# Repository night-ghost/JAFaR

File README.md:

The original pkendall64 version not works or even not compiles for me so this is easy-build version with almost the same functions

## pkendall64's original README follows

# JAFaR (Just Another Fatshark Receiver Module)

DIY OpenSource 40ch receiver OSD integrated

## This is a major refactor of MikyM0use's original code

**Changes**
* Added a favorites section which remembers the last 8 channels used ordered with the last used at the top of the list. It re-orders the list when you select a new channel.
* The scanner is continuously running in the main menu or scanner menu. This means that the RSSI values are pretty much always up to date.
* There's a timer progress bar on the right rather than a counter.
* Double-click (i.e. another press within 1 second) takes you back to the main menu.
* When in a band selection menu, favorites or autoscan a single click of the buttons selects the next or previous channel respectively.
* When a channel is selected, display the current RSSI for each receiver under the channel designator (only on the OLED display).
* Moved all strings in OLED and OSD to PROGMEM.

Make sure to use the updated TVout library from https://github.com/pkendall64/arduino-tvout as the original will cancel timer 2, which is the selection timer for this version of the receiver.

## MikyM0use's original README follows

The aim of the project is to build an opensource 40ch receiver for Fatshark goggles which has to be easy to develop,
upgrade and maintain. And, of course, it must be cheap!

* 40ch (8 channels for 5 bands, including race band)
* No external switch, or hall effect sensor, or buzzer, it must use __only__ the goggles buttons (up-down)
* Auto search feature
* It should include the “scanner” feature (see my recent project here https://github.com/MikyM0use/OLED-scanner)
* Frequency selection via OSD inside the goggles
* I tested it only with Fatshark HD but the module should work with every Fatshark with the RX external module (like Dominator V1, V2, V3, HD, HD2...)

This project uses the “RX5808” receiver module, which can be hacked to be SPI-programmed by a microcontroller (more details later).
So what I needed is a micro controller with an easy and well-know software IDE… nothing better than Arduino. So I decided to use an Atmega 328p as micro controller.

To select the frequency there's a series of menus on the screen inside the goggles, the
useful TVOUT Arduino library is perfect and requires just a couple of resistors
(http://playground.arduino.cc/Main/TVout).
A digital switch (TS5A3359) allow to switch from OSD to the normal receiving video from the quadcopter.

The project is mainly divided into two PCBs:
* one main base module
* one "diversity" daughterboard (optional)

it's also possibile to use an SPI-OLED display and use the module as standalone RX.

##Table of contents
* [Main module](#main-module)
	* [DIY Instructions](#diy-instructions)
	* [MAIN MODULE Troubleshooting](#main-module-troubleshooting)
* [Diversity module](#diversity-module)
* [OLED module](#oled-module)
* [STANDALONE mode](#standalone-mode)
* [Reference thread](#reference-thread)
* [FAQ:](#faq)
* [Donations:](#donations)

##Main module

This is the main RX module, usable alone as a 40ch receiver module, but if you connect an
"external" module, the onboard microcontroller can decide which RX module has better
reception (so-called "diversity") based on the received signal strength. Indeed, this
RX5808 modules has an analog output called RSSI proportional on the "quality" of the
received video signal. The receiving video channel (frequency) is set by the user using an OSD menu.

__MAIN MODULE (V4.0) BOM__

https://docs.google.com/spreadsheets/d/1CrZzOQHyK_d1VfHCQKwdNuoyMji0IYryI1VuffojdGA/edit?usp=sharing

__LEGACY MAIN MODULE (V3.2)__

This module is actually the same as the v4.0, but it doesn't have the buffer on the RSSI output,
and the PCB allows the use of a capacitor OR a resistor on the video out. DON'T use both! after some
tests I realized that a 10ohm resistor (and no cap) is enough.

(the back side is the same of the v4.0).

__LEGACY MAIN MODULE (V3.2) BOM__

https://docs.google.com/spreadsheets/d/1-763imBV3QsQ71GKDZH-BirTz1k32szNuJZUKQrE00g/edit?usp=sharing

###DIY Instructions

1. Remove the shield of the RX5808 module and desolder the resistor marked by the arrow. This
is the SPI-mod required to control the module with an external microcontroller.

2. Follow the instructions on the page https://www.arduino.cc/en/Tutorial/ArduinoISP to burn the bootloader (select __"Arduino Pro Mini 5v 16MHz"__ as target board)
using the pins in the upper right corner of the board

3. Use the FTDI connections in the left side of the board to upload the code present in the
Github page of the project. Please remember to copy all the subfolders of "libs" dir in the
libraries folder of Arduino (e.g. /Arduino/libraries).
Here you can find more infos and alternative methods to import the libraries:
https://www.arduino.cc/en/Guide/Libraries

4. When you power on the module, BOTH the leds (upper left corner of the pcb) must be on, and you must see a relatively stable splash screen for about 5 seconds

5. The very first time you power on the module, it need to calibrate itself. So please turn on the module with a working Vtx a couple of meter away (the video frequency doesn't matter). This process can take a while (about 30-50 seconds).

6. You can now use the "selection" buttons on the goggles to scroll up/down the menu to select the band

7. After the timout of the countdown (upper left corner of the screen) you entered the frequency selection (of the selected band)

8. Scroll up/down to select the frequency and wait the timeout

9. At this moment only one led on the module has to be ON, it means that the RX video output is routed to the video_input of the goggles. If you have a Vtx near, you should see the video coming from it.

10. If you press the "selection" buttons of the goggles now, you change the frequency by the 8 frequencies of the previously selected band.

###MAIN MODULE Troubleshooting

After the initial calibration, the module must turn on in couple of seconds and you must see the splash screen for some seconds before the "band selection" screen.
In the "band selection" screen you can see the 5 bands with the percentage of the maximum RSSI detected on that band. At least one of the band must be at 98-100%.
If you "enter" one band, every channel must shows a different percentage of RSSI, otherwise the SPI-mod of the module could be failed.

__Unable to flash/Aduino issues:__

(thanks to pHysiX for the help in this section!)
Got the error "no reply" when trying to load the firmware:
the ATmega microcontroller is not soldered properly / there is a short on some pins.
try a quick solder, clean and reflow.

Got the error "incorrect signature" when trying to load the firmware:
This means Arduino is able to pick up the ATMega, but it was not communicating as expected.
This is related to poor soldering of the crystal. It's possible to do the crystal using
an iron, but I strongly recommend using flow method/hot air to do this, to make sure you
don't short the three legs accidentally onto the metal case.

__Display issues:__

They are mostly related to poor soldering for the OSD components on the board. Go back and
reflow especially the Switch, and then just make sure to clean up and touch up all the caps
and resistors near and around the switch.

If you have an external monitor, you can bypass the digital switch by power on the module with external 5v and connecting the "video in" of the monitor on the test point marked in yellow the picture:

and you should see the splash screen and the menu.

If you connect the "video in" of the monitor to the test point marked in green, you should see the initial scanning (used to determine the % of the RSSI on each channel), this means a sequence of different "fogs" and (at least) one "good" image (for a fraction of second), if you have a Vtx + cam transmitting.

__Frequency issues:__

If the module is having trouble Setting Frequency, or you are not getting video when you are
on the right channel and frequency, make sure the SPI mod has been done, and that the RX5808
is soldered on well. Pretty hard to mess this part up.

##Diversity module

The diversity module is an optional second receiver, connected to the "main" base module, it has:
* integrated linear 5v regulator with ENABLE feature connected to the VCC of the main module.
In fact power a second module from the internal goggles voltage regulator IS VERY DANGEROUS!
* an optional operational buffer for RSSI signal (I noticed that lately modules seems to be more delicate)

please notice that because of the linear regulator it's not possibile to use a 3s battery to power the diversity module.

__DIVERSITY MODULE (V2.1) BOM__

https://docs.google.com/spreadsheets/d/1OpagubuxicmGTKqOHWwWdxZxY6wCs_DZqTYRxVoD4Tc/edit?usp=sharing

##OLED module
It's possible to use an external SPI OLED module in case of any problems with the internal OSD
or to use the module with an external monitor / different goggles.

It's important that the module has only SDA/SCL/RES/DC pins.

To use the OLED module instead of the internal OSD, uncomment  the line:

```
#define USE_OLED
```

in the file const.h

please remember to comment #define USE_DIVERSITY!

__Connections__

| ATMEGA328p pin        |  PCB silkscreen name           | OLED silkscreen name  |
| :-------------------:	|:------------------------------:| :--------------------:|
| VCC      				| 		EN 						| 		VCC 			|
| GND      				| GND 							| 					GND |
| 8      				| SSEL 							| 				SCL 	|
| A1      				| RSSI      					|   		SDA 		|
| A4 					|  NOT CONNECTED      			|    	NOT CONNECTED 	|
| 11 					| SDA      						|    DC 				|
| 13				 	| CLK      						|    RESET 				|

...or graphically:

there's also a "PCB" inside the PCBs folder, but it's just a simple adaptor.

##Standalone mode

It's possible to use the project also as a standalone receiver to be used in combination
with any external monitor or other kind of goggles.

In this case you must uncomment the line

```
#define STANDALONE
```

in the file const.h. You can use the standalone mode either with OSD or with the external SPI OLED module.

to change band/channel, the connections are the following (every normally-open momentary switch will do the job):

##Reference thread

http://www.rcgroups.com/forums/showthread.php?t=2619124 while I'm still writing the readme :)

##FAQ

why the OSD is on the blank screen?
it’s simpler because one cannot have to recognize the vsync and the hsync pulses.

why the switch is so small and hard to solder?!?
I need a small 3-way switch, if you have a "simpler" one, just tell me :)

please note that you try and use this project AT YOUR OWN RISK!

##Donations

Hardware or paypal donations to carry on the project are always accepted.

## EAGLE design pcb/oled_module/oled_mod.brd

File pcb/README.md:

PLEASE READ THIS BEFORE GO FURTHER!

THIS PCB IS VERY EXPERIMENTAL! TRY IT AT YOUR OWN RISK!

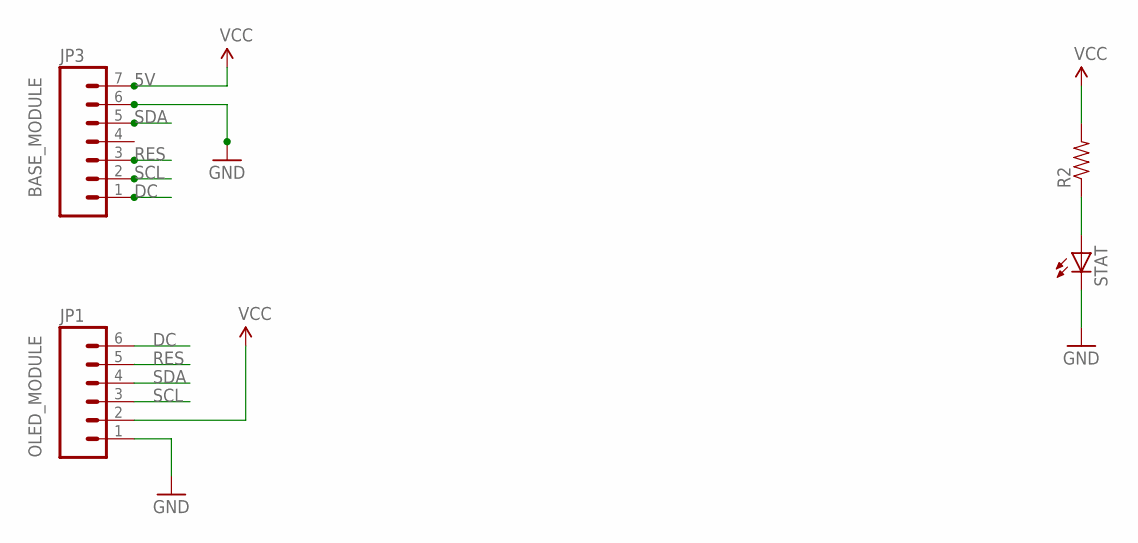
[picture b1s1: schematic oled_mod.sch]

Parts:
JP1: M06SILK_FEMALE_PTH; 1X06
JP3: M07; 1X07
R2: RESISTOR0805-RES; 0805
STAT: LEDCHIP-LED0805; CHIP-LED0805

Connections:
5V: JP1.2, JP3.7, R2.2
DC: JP1.6, JP3.1
GND: JP1.1, JP3.6, STAT.C
unnamed: R2.1, STAT.A
RES: JP1.5, JP3.3
SCL: JP1.3, JP3.2
SDA: JP1.4, JP3.5

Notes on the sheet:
BASE_MODULE
OLED_MODULE

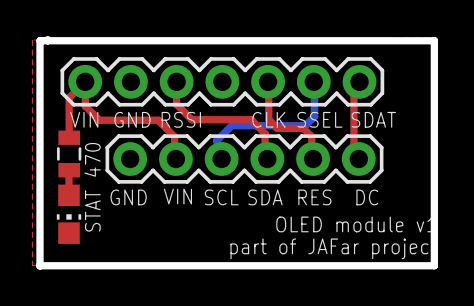
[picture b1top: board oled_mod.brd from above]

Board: 2 copper layers, 21.9 x 12.6 mm, 4 parts (0 on the bottom side), 7 nets.

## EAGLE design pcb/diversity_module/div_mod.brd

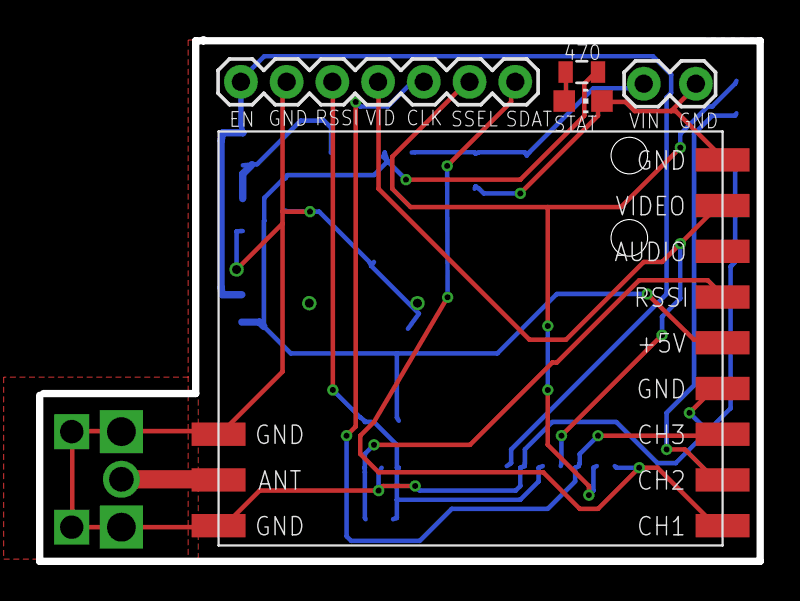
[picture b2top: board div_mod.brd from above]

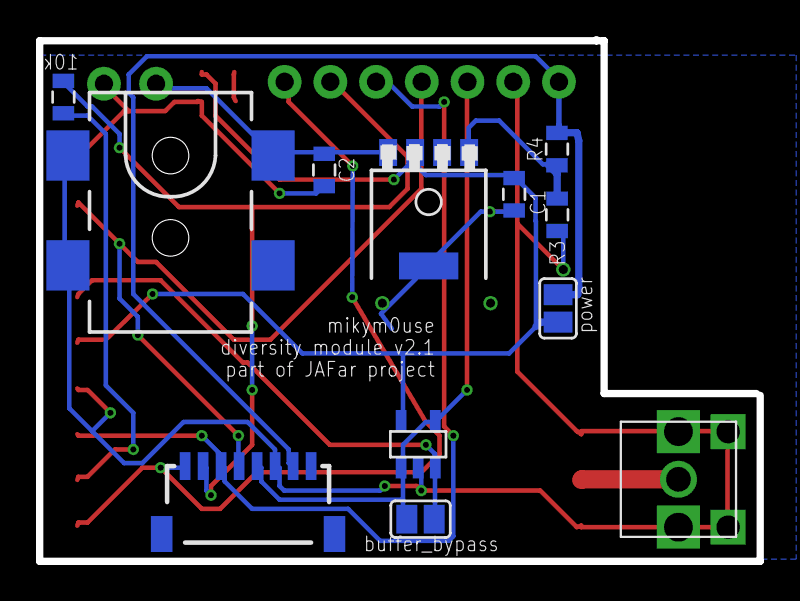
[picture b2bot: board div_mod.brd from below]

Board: 2 copper layers, 40.0 x 29.0 mm, 17 parts (12 on the bottom side), 14 nets.

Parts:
C1, C2: 1uf; 0805
IC3: OPA336N; SOT23-5
JP1: 5.5x2.1mm Barrel; POWER_JACK_SMD
JP2: 1X02_LOCK
JP3: 1X07
R1, R2: 0805
R3: 10k; 0805
R4: 100k; 0805
RECEIVER_A: RX5808_A; RX5808
SJ1, SJ2: SJ
STAT: CHIP-LED0805
U$1: SMA_ANTENNA; SMA_CONNECTOR
U$3: EB-85ASMD; EB-85A
V1: LP38692P; TO252-51

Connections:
5V: C1.1, IC3.5, R2.2, RECEIVER_A.+5V, SJ1.2, V1.OUT
ENABLE: R3.2, R4.1, V1.EN
ENABLE_P: JP3.7, R4.2, SJ1.1, U$3.7
GND: C1.2, C2.2, IC3.2, JP1.GND, JP1.P$4, JP2.1, JP3.6, R3.1, RECEIVER_A.GND1, RECEIVER_A.GND2, RECEIVER_A.GND3, RECEIVER_A.GND4, STAT.C, U$1.P$1, U$1.P$2, U$1.P$3, U$1.P$4, U$3.6, V1.GND
unnamed: R1.1, RECEIVER_A.CH2
unnamed: R2.1, STAT.A
unnamed: RECEIVER_A.ANT, U$1.ANT
RSSI_B: IC3.1, IC3.4, JP3.5, SJ2.2, U$3.5
RSSI_MOD: IC3.3, RECEIVER_A.RSSI, SJ2.1
RXVIDOUT2: JP3.4, RECEIVER_A.VIDEO, U$3.4
SPI_CLK: JP3.3, RECEIVER_A.CH3, U$3.3
SPI_DATA: JP3.1, RECEIVER_A.CH1, U$3.1
SPI_SEL_B: JP3.2, R1.2, U$3.2
VIN_UNREG: C2.1, JP1.VIN0, JP2.2, V1.IN

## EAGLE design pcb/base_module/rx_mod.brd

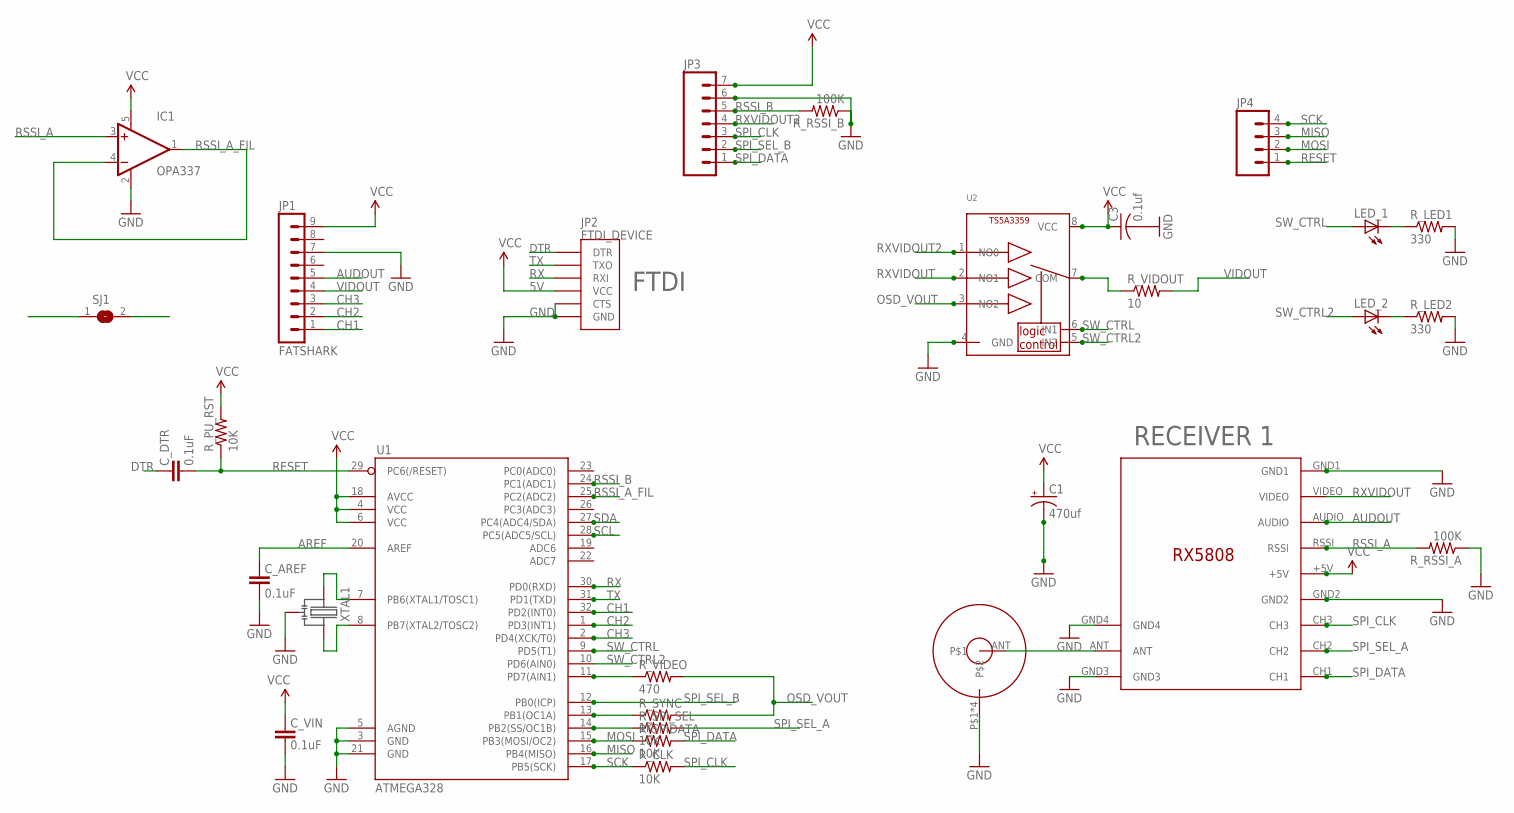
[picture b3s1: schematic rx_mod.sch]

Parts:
C1: 470uf; EIA7343
C3: 0.1uf; C0603
C_AREF: 0.1uF; 0603-CAP
C_DTR: 0.1uF; 0603-CAP
C_VIN: 0.1uF; 0603-CAP
IC1: OPA336N; SOT23-5
JP1: FATSHARK; MA09-1
JP2: FTDI_DEVICE; FTDI_DEVICE_SIDE
JP3: M07; 1X07
JP4: M04PTH; 1X04
LED_1, LED_2: LEDSML0603; SML0603
RECEIVER_A: RX5808_A; RX5808
R_CLK: 10K; R0805
R_LED1, R_LED2: 330; R0603
R_PU_RST: 10K; 0603-RES
R_RSSI_A: 100K; 0603-RES
R_RSSI_B: 100K; 0603-RES
R_SPIDATA: 10K; R0805
R_SPI_SEL: 10K; R0805
R_SYNC: 1K; R0805
R_VIDEO: 470; R0805
R_VIDOUT: 10; R0805
SJ1: SJ
U1: ATMEGA328; TQFP32-08
U2: TS5A3359; VFSOP-8
U$1: SMA_ANTENNA; SMA_CONNECTOR
XTAL1: CSTCE16M0V53-R0

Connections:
5V: C1.A (+), C3.1, C_VIN.2, IC1.5 (V+), JP1.9, JP2.P$4 (VCC), JP3.7, RECEIVER_A.+5V, R_PU_RST.2, U1.4 (VCC), U1.6 (VCC), U1.18 (AVCC), U2.8 (VCC)
AREF: C_AREF.2, U1.20 (AREF)
AUDOUT: JP1.5, RECEIVER_A.AUDIO
CH1: JP1.1, U1.32 (PD2(INT0))
CH2: JP1.2, U1.1 (PD3(INT1))
CH3: JP1.3, U1.2 (PD4(XCK/T0))
DTR: C_DTR.2, JP2.P$1 (DTR)
GND: C1.C (-), C3.2, C_AREF.1, C_VIN.1, IC1.2 (V-), JP1.7, JP2.P$5 (CTS), JP2.P$6 (GND), JP3.6, RECEIVER_A.GND1, RECEIVER_A.GND2, RECEIVER_A.GND3, RECEIVER_A.GND4, R_LED1.2, R_LED2.2, R_RSSI_A.1, R_RSSI_B.1, U1.3 (GND), U1.5 (AGND), U1.21 (GND), U2.4 (GND), U$1.P$1, U$1.P$2, U$1.P$3, U$1.P$4, XTAL1.2
MISO: JP4.3, U1.16 (PB4(MISO))
MOSI: JP4.2, R_SPIDATA.1, U1.15 (PB3(MOSI/OC2))
unnamed: U1.8 (PB7(XTAL2/TOSC2)), XTAL1.3
unnamed: U1.7 (PB6(XTAL1/TOSC1)), XTAL1.1
unnamed: LED_1.C, R_LED1.1
unnamed: R_SPI_SEL.1, U1.14 (PB2(SS/OC1B))
unnamed: RECEIVER_A.ANT, U$1.ANT
unnamed: R_VIDOUT.1, U2.7 (COM)
unnamed: R_SYNC.1, U1.13 (PB1(OC1A))
unnamed: R_VIDEO.1, U1.11 (PD7(AIN1))
unnamed: LED_2.C, R_LED2.1
OSD_VOUT: R_SYNC.2, R_VIDEO.2, U2.3 (NO2)
RESET: C_DTR.1, JP4.1, R_PU_RST.1, U1.29 (PC6(/RESET))
RSSI_A: IC1.3 (+IN), RECEIVER_A.RSSI, R_RSSI_A.2, SJ1.1
RSSI_A_FIL: IC1.1 (OUT), IC1.4 (-IN), SJ1.2, U1.25 (PC2(ADC2))
RSSI_B: JP3.5, R_RSSI_B.2, U1.24 (PC1(ADC1))
RX: JP2.P$3 (RXI), U1.30 (PD0(RXD))
RXVIDOUT: RECEIVER_A.VIDEO, U2.2 (NO1)
RXVIDOUT2: JP3.4, U2.1 (NO0)
SCK: JP4.4, R_CLK.1, U1.17 (PB5(SCK))
SCL: U1.28 (PC5(ADC5/SCL))
SDA: U1.27 (PC4(ADC4/SDA))
SPI_CLK: JP3.3, RECEIVER_A.CH3, R_CLK.2
SPI_DATA: JP3.1, RECEIVER_A.CH1, R_SPIDATA.2
SPI_SEL_A: RECEIVER_A.CH2, R_SPI_SEL.2
SPI_SEL_B: JP3.2, U1.12 (PB0(ICP))
SW_CTRL: LED_1.A, U1.9 (PD5(T1)), U2.6 (IN1)
SW_CTRL2: LED_2.A, U1.10 (PD6(AIN0)), U2.5 (IN2)
TX: JP2.P$2 (TXO), U1.31 (PD1(TXD))
VIDOUT: JP1.4, R_VIDOUT.2

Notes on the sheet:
RECEIVER 1
FTDI
OPA337

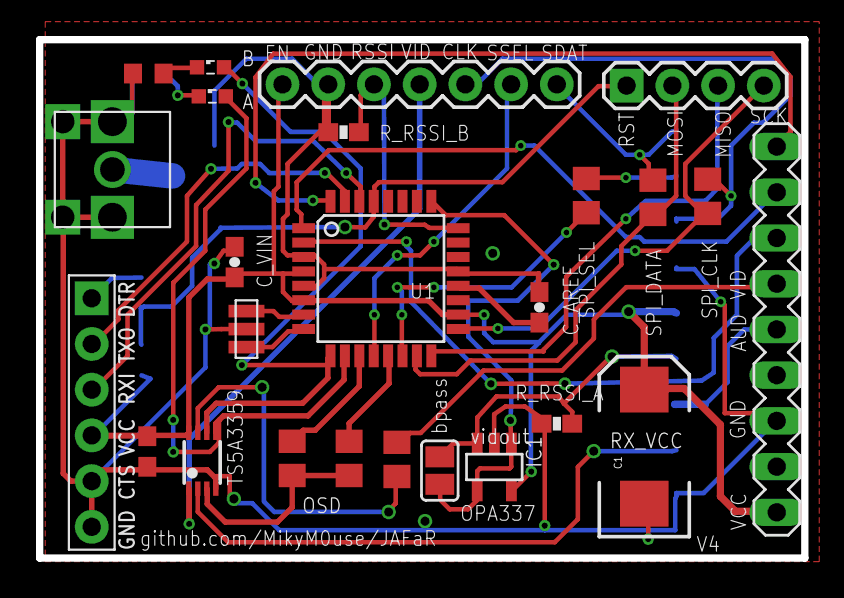
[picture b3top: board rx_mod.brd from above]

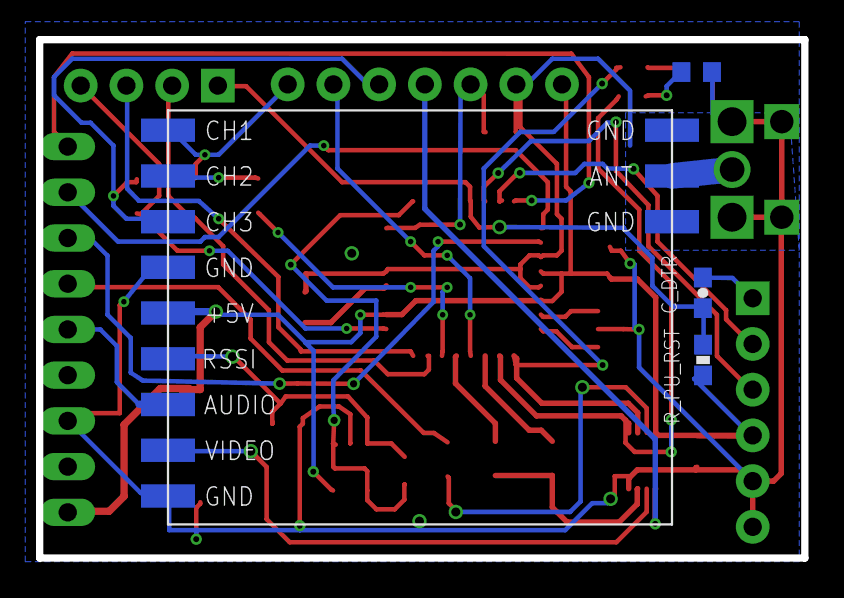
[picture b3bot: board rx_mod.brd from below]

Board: 2 copper layers, 42.5 x 28.8 mm, 29 parts (4 on the bottom side), 36 nets.

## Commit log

2016-04-15 code reworked
2016-04-15 diversity support beta version UNTESTED
2016-04-15 diversity ready version - TESTED
2016-04-15 first version - antenna position reworked
2016-04-17 debug log on eeprom
2016-04-19 regulator, buffer and new SMA connetor. v1.1
2016-04-19 new SMA connetor
2016-04-19 add BOM
2016-04-19 typos
2016-04-20 LDO name replaced
2016-04-22 v3.2
2016-04-22 adding some docs
2016-04-22 adding some imgs
2016-04-22 some more docs
2016-04-22 formatting
2016-04-22 removing wrong version of diversity module
2016-04-22 removing wrong version of pcbs
2016-04-22 diversity module v1.1
2016-05-20 base module V3.2
2016-05-20 moved to subdir
2016-05-20 moved diversity board to testing branch
2016-05-20 diversity module v2.0
2016-05-20 base module v4.0
2016-05-20 removed diversity module infos from master branch
2016-05-20 diversity board V2.0
2016-05-27 new version pcb images
2016-05-27 diversity board v2.1
2016-05-27 added arrow
2016-05-27 BOM update
2016-06-20 add force_first
2016-06-20 fix cap on image
2016-06-20 typos...
2016-06-21 added DIY section
2016-06-21 render *
2016-06-22 readme test points
2016-06-22 replaced png with jpg
2016-06-22 add modules version
2016-06-22 TV.delay and USE_DIVERSITY
2016-06-23 force TV disable
2016-06-23 force OSD disable
2016-06-23 ifdef typo
2016-06-23 dividing OSD and OLED code
2016-06-25 add splash screen
2016-06-26 first OLED version, OSD must be fixed
2016-06-26 force timer=0 at the end of submenu selection
2016-06-26 oled beta testing...
2016-06-26 OLED scanner mode
2016-06-26 band rssi on OLED main menu
2016-06-26 some initial docs
2016-06-27 first standalone version
2016-06-30 add looptime and fixes...
2016-07-05 add oled pcb and U8g lib, fix docs
2016-07-05 fix docs...
2016-07-05 spi-mod docs
2016-07-05 image dim
2016-07-05 spi-mod image dimension
2016-07-05 image dim reductions
2016-07-08 Fixed TVOut library to support old Fatshark Dominator V1.
2016-07-09 fix minor bugs and add connections picture
2016-07-09 standalone doc
2016-07-09 minor changes to doc
2016-07-09 first commit on autoscan
2016-07-09 fix a bug with RSSI reading
2016-07-09 fix RSSI read avg bug
2016-07-09 autoscan on oled too
2016-07-17 solved a bug in the submenu selection
2016-07-30 switch gnd and vcc on silkscreen
2016-07-30 minor bug fixes
2016-08-02 flip OLED screen define
2016-08-03 initial timer value changed to 5 seconds
2016-09-18 add I2C oled support
2016-09-20 Major refactor for interupt driven operation. Also uses updated TVout library from my repository.
2016-09-20 Add platformio build files
2016-09-24 use platformio library manager
2016-09-24 Make the scanner work continuously
    When in the MAILMENU or SCANNER mode the scanner is always updating RSSI values.
    This means we can go to the autoscan and scanner menus very quickly and RSSI values are always at the latest.
2016-09-24 Update README with changes
2016-09-24 Better handling of empty slots in the favourites list.
2016-09-24 Use hardware SPI for talking to the receiver.
2016-09-25 Display the RSSI from each of the receivers when on a selected channel under the channel designator.
2016-09-25 More tidy up and consistency
    Use a common method for all band/autoscan/favorites display.
2016-09-26 Move all the strings from OLED and OSD to progmem
2017-03-03 it works now!
2017-03-03 latest from grandparents

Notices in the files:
parts and their libraries:
SparkFun-Connectors: Licensing: Creative Commons ShareAlike 4.0 International - https://creativecommons.org/licenses/by-sa/4.0
